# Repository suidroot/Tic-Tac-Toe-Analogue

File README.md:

# Tic-Tac-Toe-Analogue

This is a project to create an tic tac toe game using only analogue logic

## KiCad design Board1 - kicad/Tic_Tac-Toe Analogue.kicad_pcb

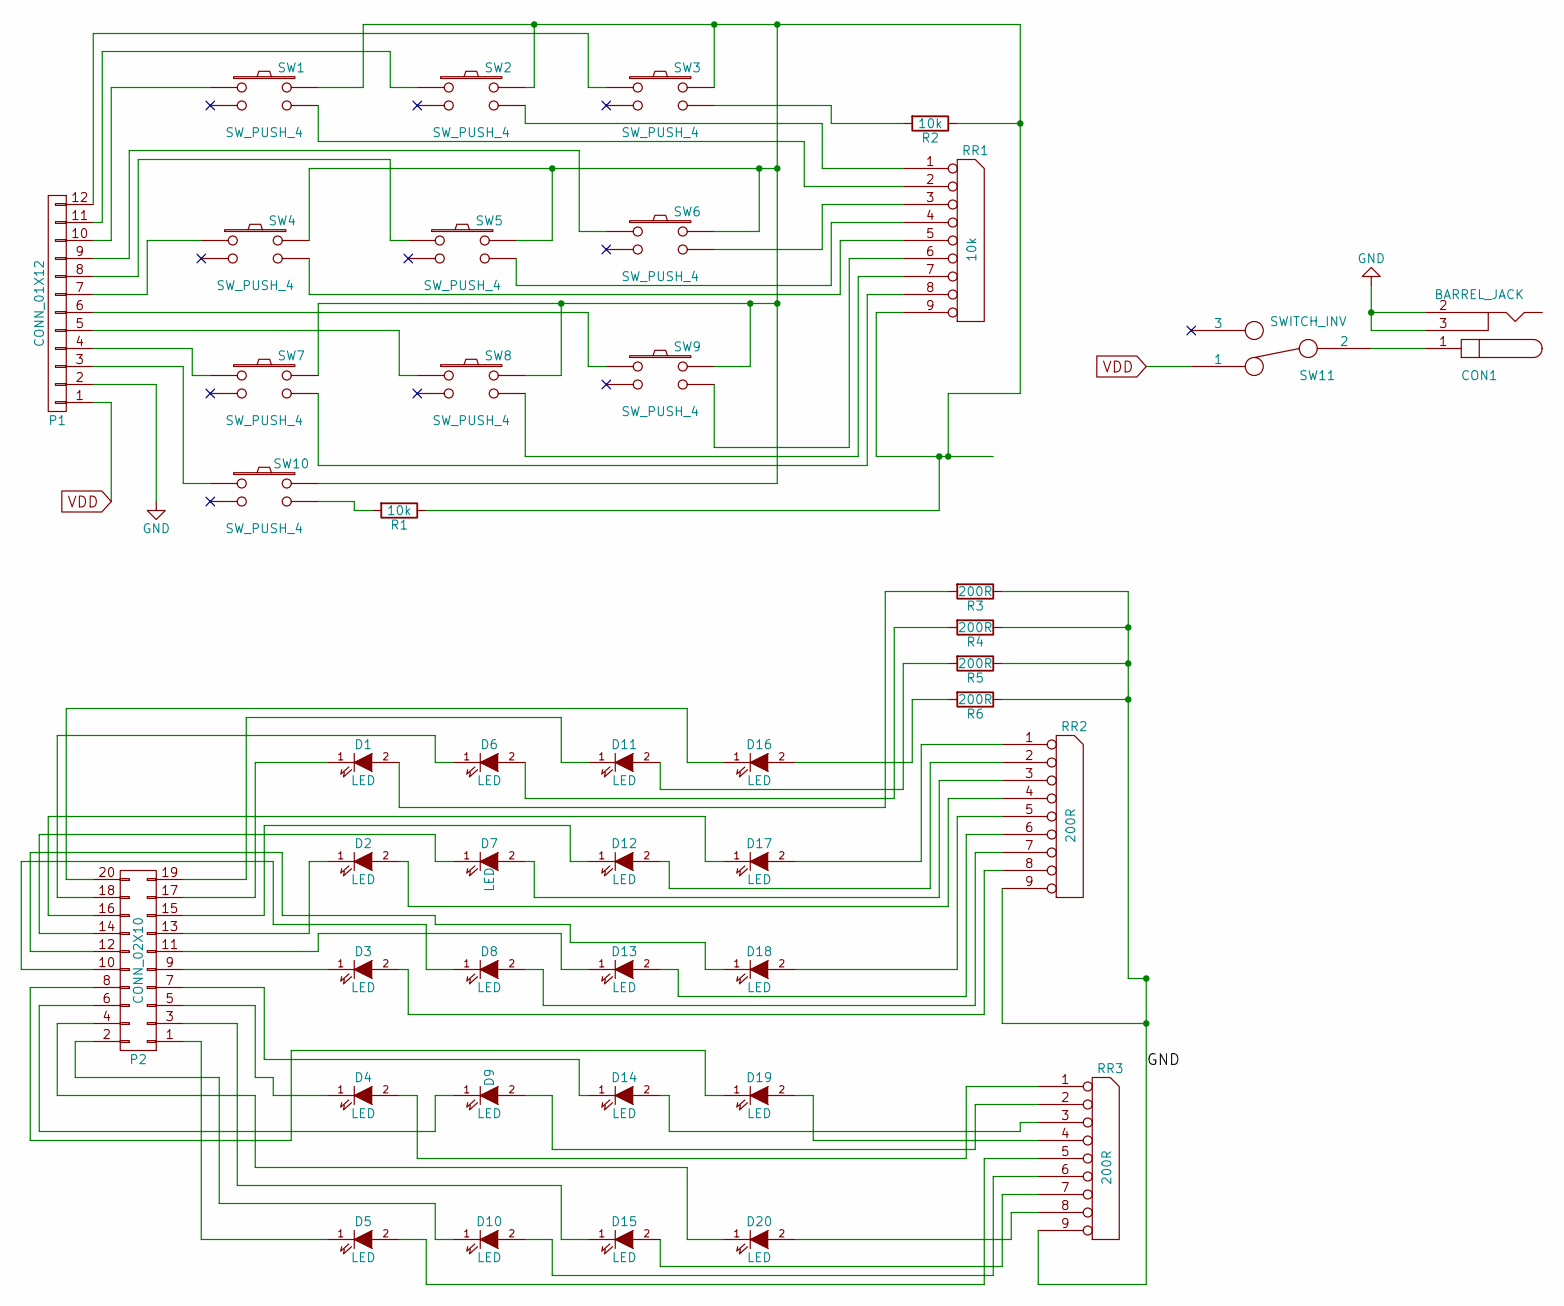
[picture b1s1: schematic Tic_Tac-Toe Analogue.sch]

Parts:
CON1: BARREL_JACK
D1, D2, D3, D4, D5, D6, D7, D8, D9, D10, D11, D12, D13, D14, D15, D16, D17, D18, D19, D20: LED; LED_D5.0mm
P1: CONN_01X12; Pin_Header_Straight_1x12
P2: CONN_02X10; Pin_Header_Straight_2x10
R1, R2: 10k; R_Axial_DIN0207_L6.3mm_D2.5mm_P10.16mm_Horizontal
R3, R4, R5, R6: 200R; R_Axial_DIN0207_L6.3mm_D2.5mm_P10.16mm_Horizontal
RR1: 10k; TerminalBlock_Pheonix_MPT-2.54mm_9pol
RR2, RR3: 200R; TerminalBlock_Pheonix_MPT-2.54mm_9pol
SW1, SW2, SW3, SW4, SW5, SW6, SW7, SW8, SW9, SW10: SW_PUSH_4; SW_TH_Tactile_Omron_B3F-10xx
SW11: SWITCH_INV; SW_Micro_SPST

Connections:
GND: CON1.2, CON1.3, P1.2, R3.1, R4.1, R5.1, R6.1, RR2.9, RR3.9
unnamed: CON1.1, SW11.2
unnamed: D1.1 (K), P2.17
unnamed: D1.2 (A), R3.2
unnamed: D2.1 (K), P2.13
unnamed: D2.2 (A), RR2.4
unnamed: D3.1 (K), P2.9
unnamed: D3.2 (A), RR2.8
unnamed: D4.1 (K), P2.5
unnamed: D4.2 (A), RR3.1 (COM)
unnamed: D5.1 (K), P2.1
unnamed: D5.2 (A), RR3.5
unnamed: D6.1 (K), P2.18
unnamed: D6.2 (A), R4.2
unnamed: D7.1 (K), P2.14
unnamed: D7.2 (A), RR2.3
unnamed: D8.1 (K), P2.10
unnamed: D8.2 (A), RR2.7
unnamed: D9.1 (K), P2.6
unnamed: D9.2 (A), RR3.2
unnamed: D10.1 (K), P2.2
unnamed: D10.2 (A), RR3.6
unnamed: D11.1 (K), P2.19
unnamed: D11.2 (A), R5.2
unnamed: D12.1 (K), P2.15
unnamed: D12.2 (A), RR2.2
unnamed: D13.1 (K), P2.11
unnamed: D13.2 (A), RR2.6
unnamed: D14.1 (K), P2.7
unnamed: D14.2 (A), RR3.3
unnamed: D15.1 (K), P2.3
unnamed: D15.2 (A), RR3.7
unnamed: D16.1 (K), P2.20
unnamed: D16.2 (A), R6.2
unnamed: D17.1 (K), P2.16
unnamed: D17.2 (A), RR2.1 (COM)
unnamed: D18.1 (K), P2.12
unnamed: D18.2 (A), RR2.5
unnamed: D19.1 (K), P2.8
unnamed: D19.2 (A), RR3.4
unnamed: D20.1 (K), P2.4
unnamed: D20.2 (A), RR3.8
unnamed: P1.3, SW10.1
unnamed: P1.4, SW7.1
unnamed: P1.5, SW8.1
unnamed: P1.6, SW9.1
unnamed: P1.7, SW4.1
unnamed: P1.8, SW5.1
unnamed: P1.9, SW6.1
unnamed: P1.10, SW1.1
unnamed: P1.11, SW2.1
unnamed: P1.12, SW3.1
unnamed: R1.1, R2.1, RR1.9, SW1.2, SW2.2, SW3.2, SW4.2, SW5.2, SW6.2, SW7.2, SW8.2, SW9.2, SW10.2
unnamed: R1.2, SW10.3
unnamed: R2.2, SW3.3
unnamed: RR1.1 (COM), SW2.3
unnamed: RR1.2, SW1.3
unnamed: RR1.3, SW6.3
unnamed: RR1.4, SW5.3
unnamed: RR1.5, SW4.3
unnamed: RR1.6, SW9.3
unnamed: RR1.7, SW8.3
unnamed: RR1.8, SW7.3
VDD: P1.1, SW11.1

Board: 2 copper layers, 41 parts (0 on the bottom side), 33 nets, no tracks yet.

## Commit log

2017-02-21 Work on Top Board
